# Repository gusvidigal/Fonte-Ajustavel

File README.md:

# Trabalho 1: Fonte de Tensão Ajustável
Integrantes:
- Bruno Dias de Campos Filho
- Cleyton José Rodrigues Macedo
- Gustavo Vidigal Schulgin
- Kauã Benjamin Trombim Silva

## Descrição do Projeto
Nosso trabalho consiste na confecção de uma Fonte de Tensão Ajustável, com capacidade de fornecer de 3V a 12V. 
Ela foi feita utilizando um transformador, para reduzir a tensão da tomada; uma ponte de diodos, para retificar as ondas da corrente alternada; 
um capacitor, para sustentar a voltagem; um diodo zenner, para restringir a voltagem para 12V; e um potenciômetro, associado a um transistor, para regulagem.

Observação: Devido à queima do transformador utilizado no projeto (Transformador 3) na véspera da apresentação, não tivemos tempo de reajustar o nosso projeto para outro transformador. Por isso, nossa fonte forneceu um pouco menos da voltagem máxima (

## Vídeo Explicativo sobre o Projeto
[Clique aqui](https://drive.google.com/file/d/1hXpF5IvrMOFee8N-jfMH2JrUbjJo6d3g/view?usp=drive_link)

## Cotação dos Itens
| Item                |     Preço               |
|---------------------|-------------------------|
| Potenciômetro 10K   | R$9,40                  |
| Ponte de diodos W10 | ~R$2,00                 |
| Transistor 2N2222   | ~R$0,76                 |
| Capacitor 470μF 35V | ~R$1,11                 |
| Led Vermelho 5mm    | ~R$0,21                 |
| 3x Resistor 4k7Ω    | ~R$0,36                 |
| 3x Resistor 1KΩ     | ~R$0,39                 |
| Resistor 200Ω       | ~R$0,15                 |
| Resistor 100Ω       | ~R$0,13                 |
| TOTAL:              | aproximadamente R$14,51 |

## Link do projeto no Falstad
[Clique aqui](https://tinyurl.com/288thzfg)

## Projeto no PCB e no EAGLE

## Imagens do Projeto

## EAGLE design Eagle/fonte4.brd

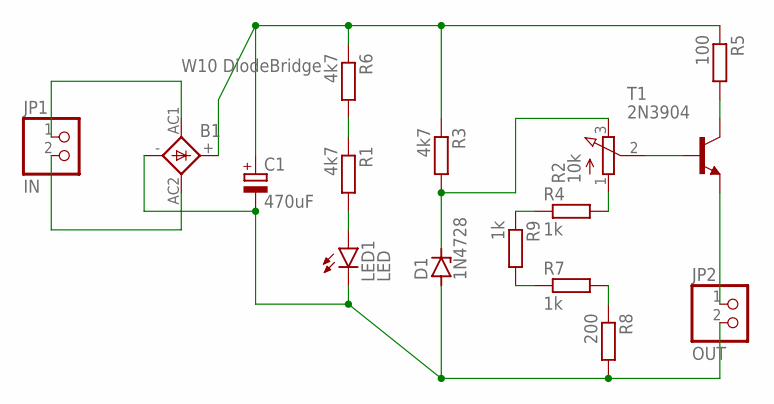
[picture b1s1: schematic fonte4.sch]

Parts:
B1: W10 DiodeBridge; 1KAB
C1: 470uF; E5-10,5
D1: 1N4728; DO41Z10
JP1: IN; 1X02
JP2: OUT; 1X02
LED1: LED; LED5MM
R1, R3, R6: 4k7; 0204/7
R2: 10k; 3RP/1610N
R4, R7, R9: 1k; 0204/7
R5: 100; 0204/7
R8: 200; 0204/7
T1: 2N3904; TO92

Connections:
unnamed: B1.AC2, JP1.2
unnamed: B1.AC1, JP1.1
unnamed: B1.+, C1.+, R3.1, R5.1, R6.1
unnamed: B1.-, C1.-, D1.A, JP2.2, LED1.K (C), R8.2
unnamed: LED1.A, R1.2
unnamed: D1.C, R2.3 (E), R3.2
unnamed: R2.1 (A), R4.2
unnamed: R2.2 (S), T1.2 (B)
unnamed: JP2.1, T1.3 (E)
unnamed: R5.2, T1.1 (C)
unnamed: R1.1, R6.2
unnamed: R4.1, R9.1
unnamed: R7.1, R9.2
unnamed: R7.2, R8.1

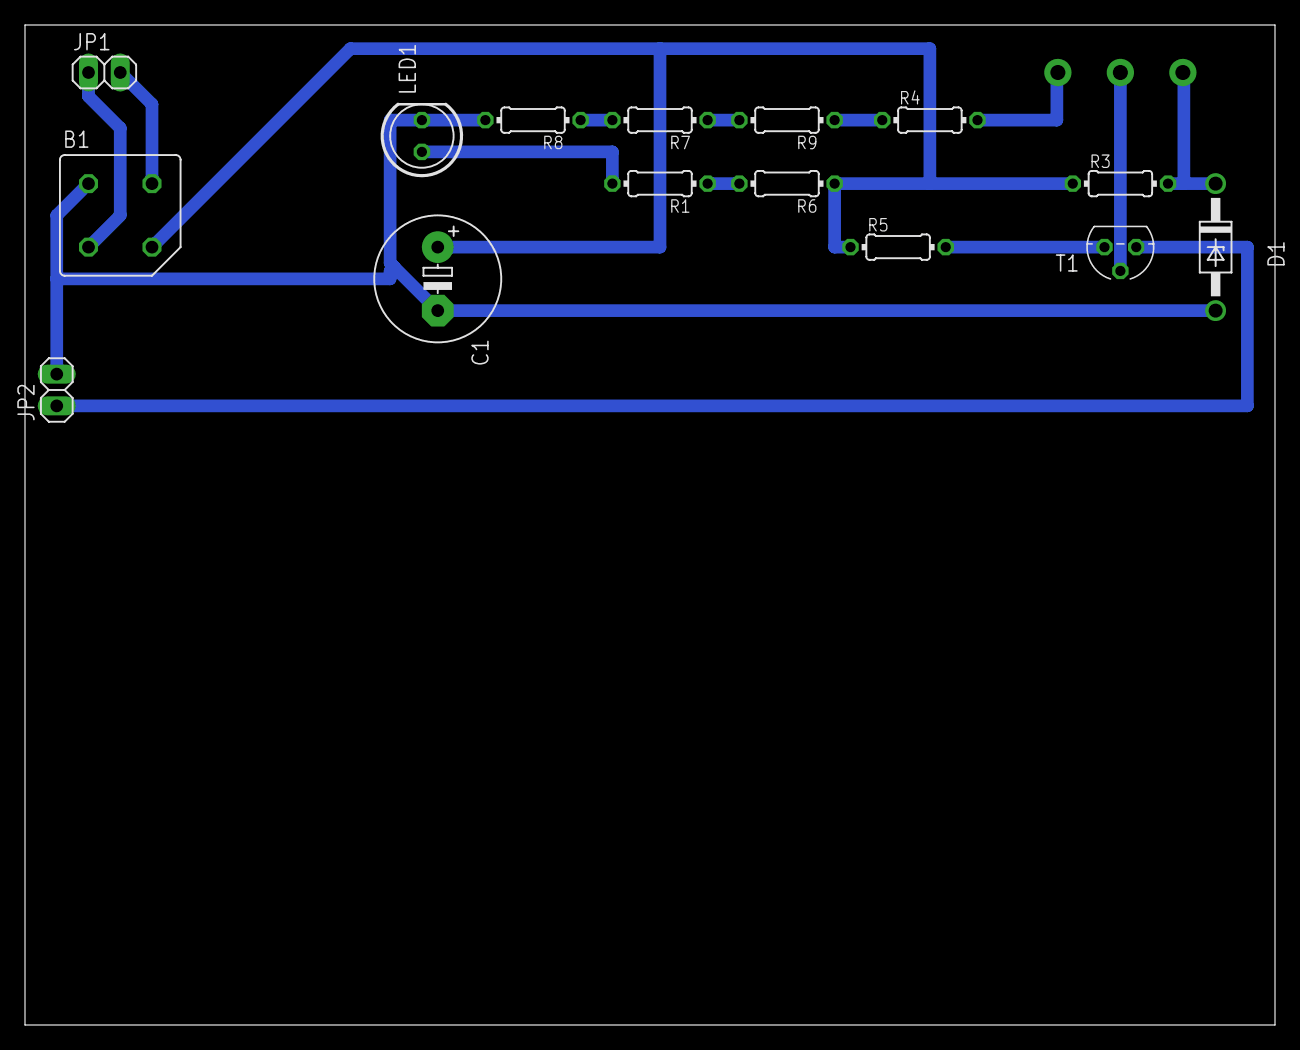
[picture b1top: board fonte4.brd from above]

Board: 2 copper layers, 100.0 x 80.0 mm, 16 parts (1 on the bottom side), 14 nets.

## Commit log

2025-07-04 Create teste
